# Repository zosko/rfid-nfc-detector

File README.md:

## RFID 125Khz / NFC 13.56Mhz detector

### Design

Board|PCB
------|------
|

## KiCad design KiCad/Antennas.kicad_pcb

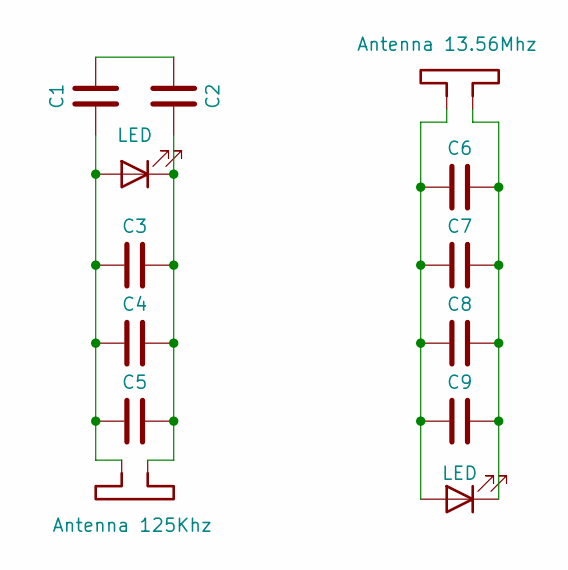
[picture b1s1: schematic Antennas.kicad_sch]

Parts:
AE1: Antenna 125Khz; 125khz
AE2: Antenna 13.56Mhz; 13.56Mhz
C1, C2, C3: 10nF; C_0805_2012Metric_Pad1.18x1.45mm_HandSolder
C4, C5: 1nF; C_0805_2012Metric_Pad1.18x1.45mm_HandSolder
C6: 82pF; C_0805_2012Metric_Pad1.18x1.45mm_HandSolder
C7: C7; C_0805_2012Metric_Pad1.18x1.45mm_HandSolder
C8: C8; C_0805_2012Metric_Pad1.18x1.45mm_HandSolder
C9: C9; C_0805_2012Metric_Pad1.18x1.45mm_HandSolder
D1, D2: LED; LED_0805_2012Metric_Pad1.15x1.40mm_HandSolder

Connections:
unnamed: AE1.1, C1.1, C3.1, C4.1, C5.1, D1.2 (A)
unnamed: C1.2, C2.1
unnamed: AE1.2, C2.2, C3.2, C4.2, C5.2, D1.1 (K)
unnamed: AE2.1, C6.1, C7.1, C8.1, C9.1, D2.2 (A)
unnamed: AE2.2, C6.2, C7.2, C8.2, C9.2, D2.1 (K)

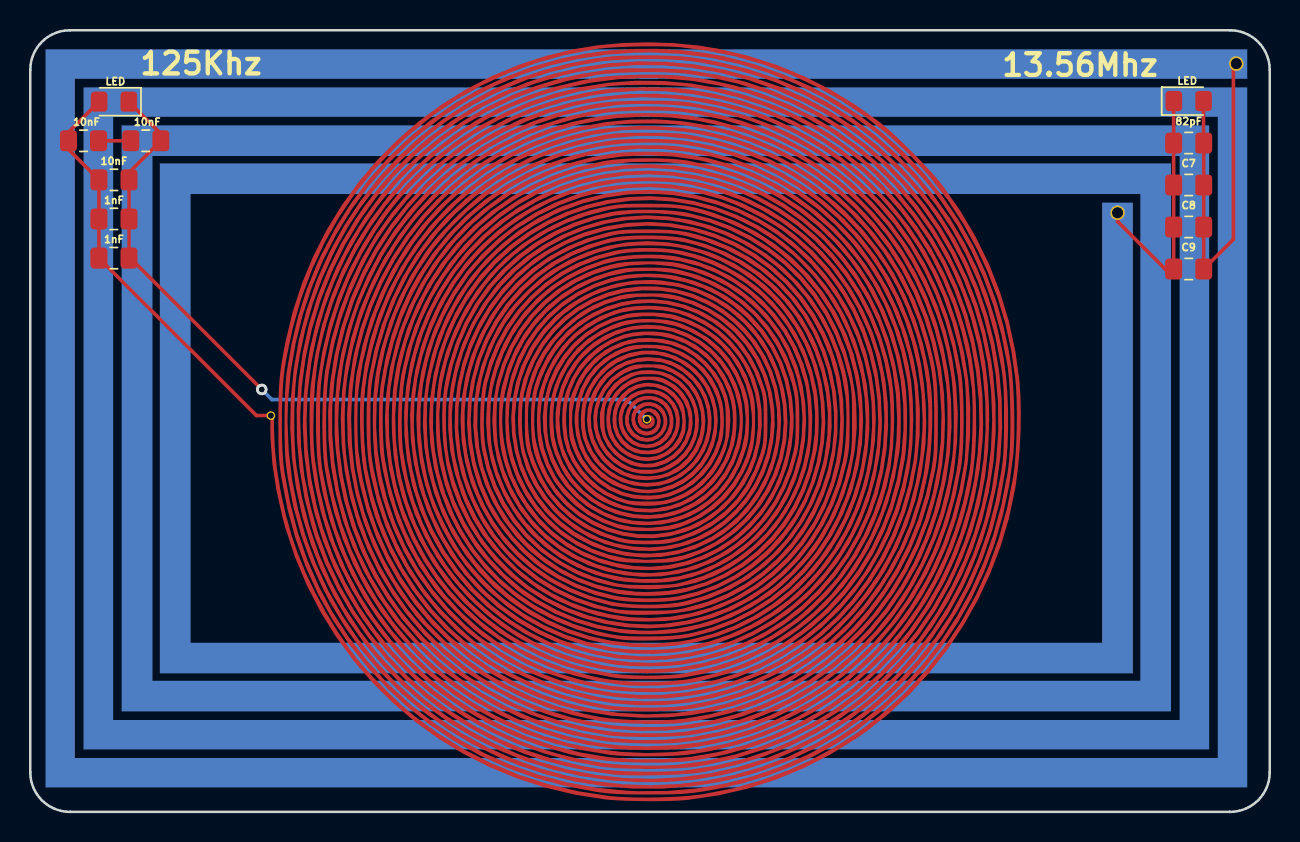
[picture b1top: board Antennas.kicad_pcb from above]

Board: 2 copper layers, 85.6 x 54.0 mm, 13 parts (1 on the bottom side), 5 nets.
